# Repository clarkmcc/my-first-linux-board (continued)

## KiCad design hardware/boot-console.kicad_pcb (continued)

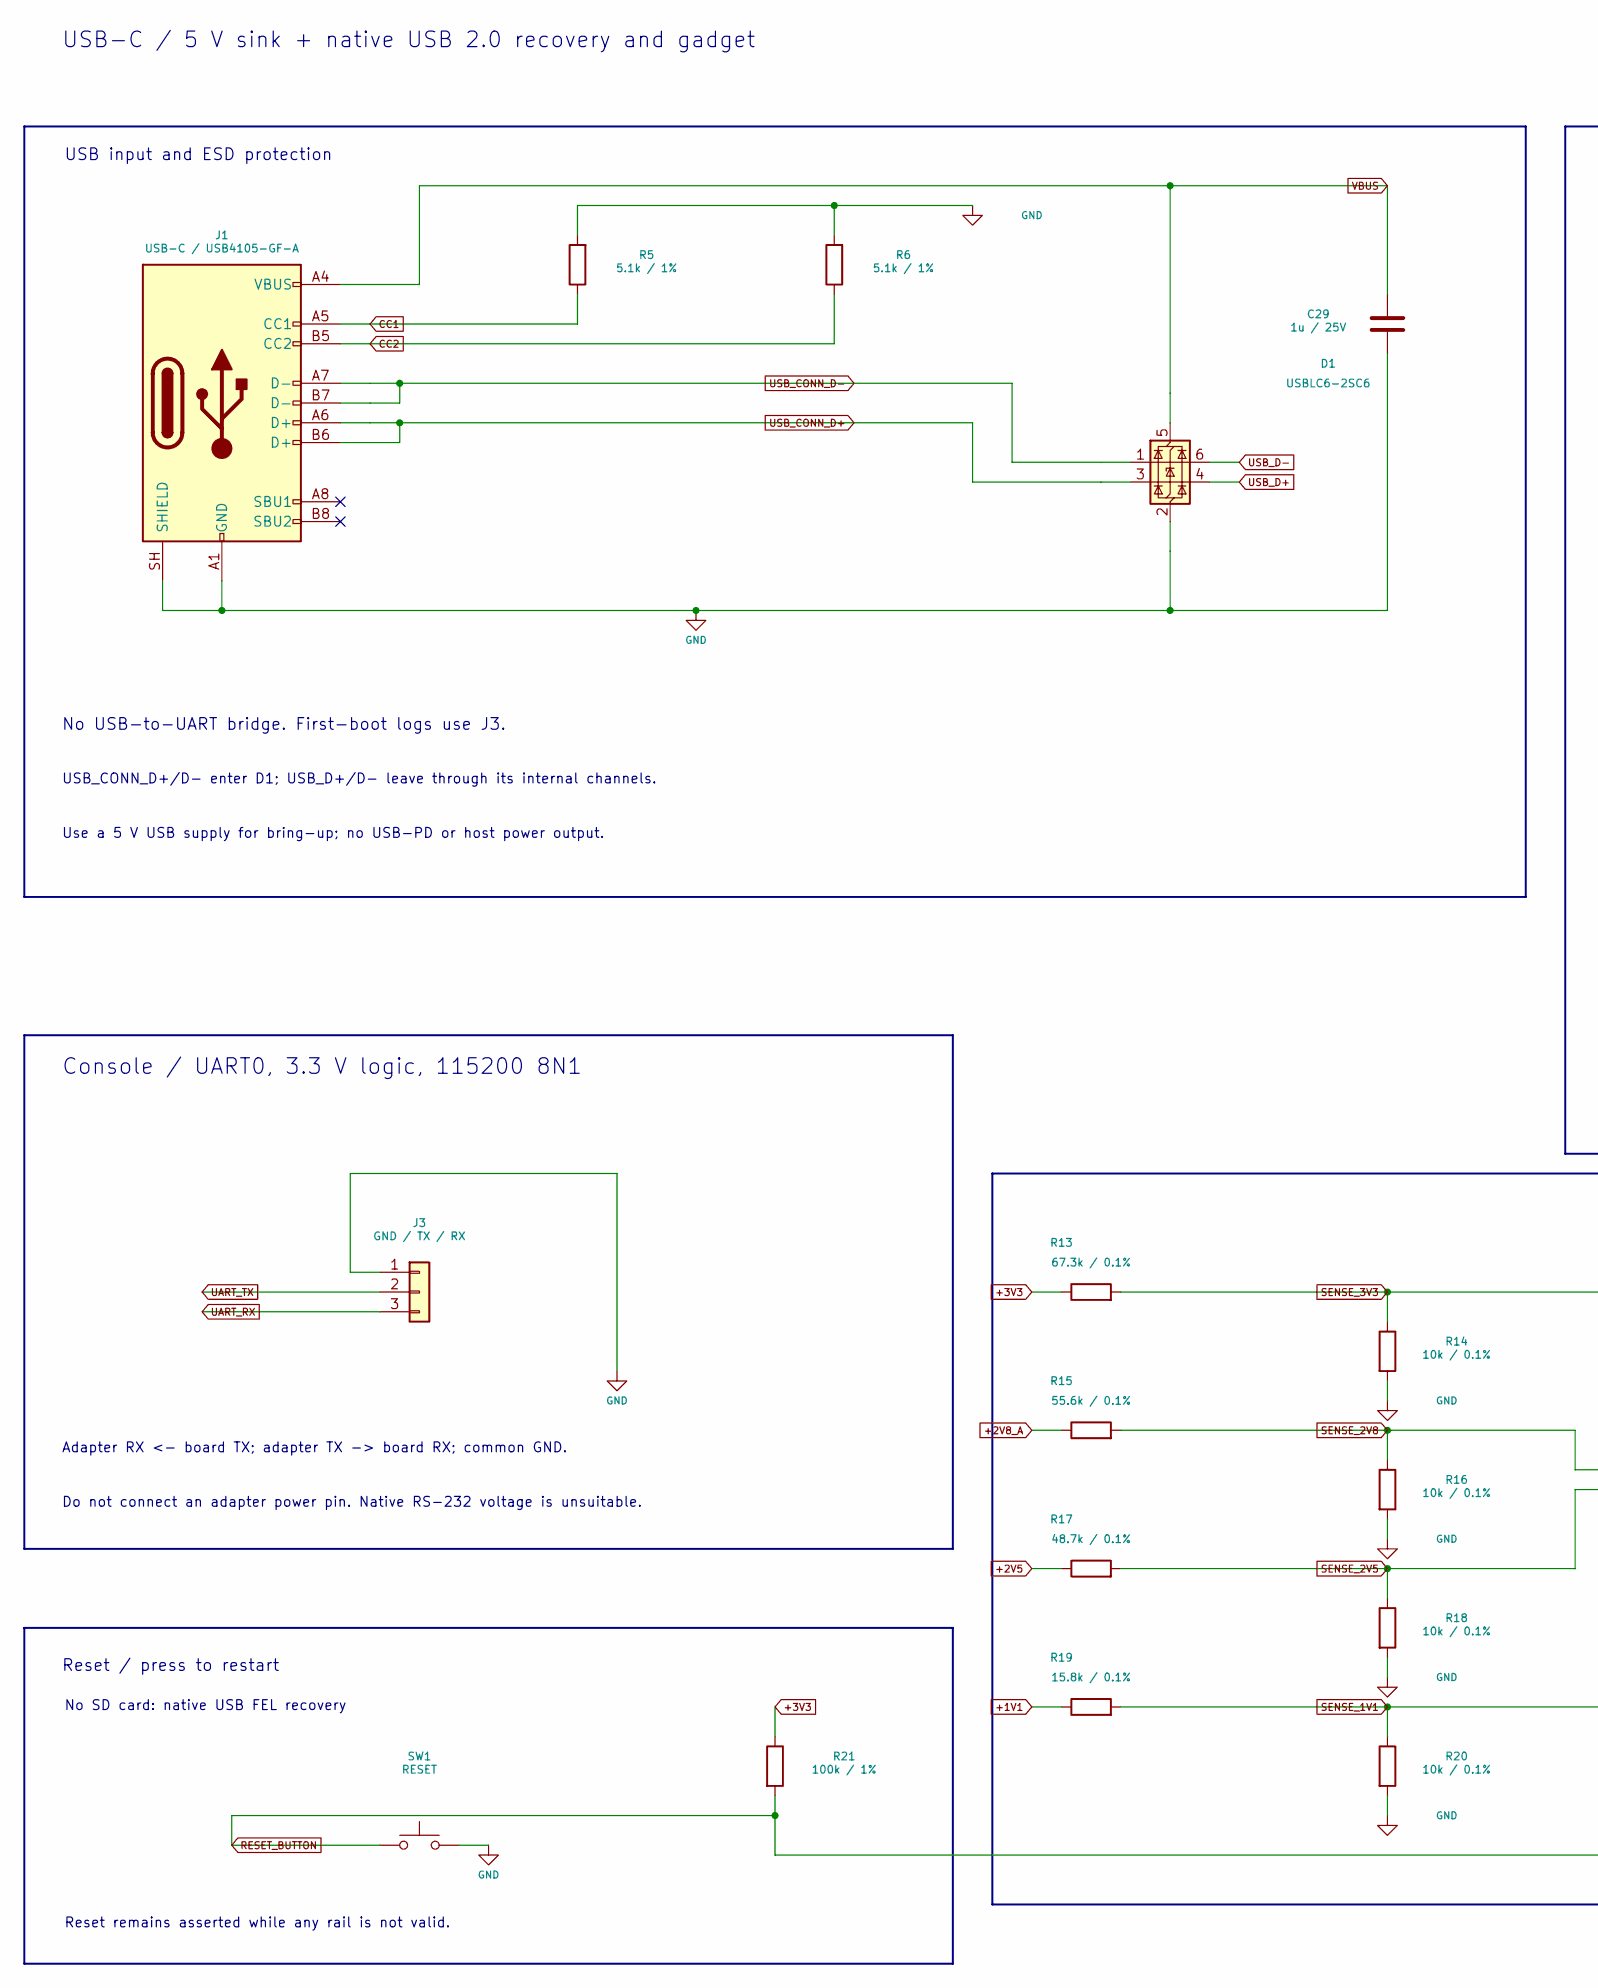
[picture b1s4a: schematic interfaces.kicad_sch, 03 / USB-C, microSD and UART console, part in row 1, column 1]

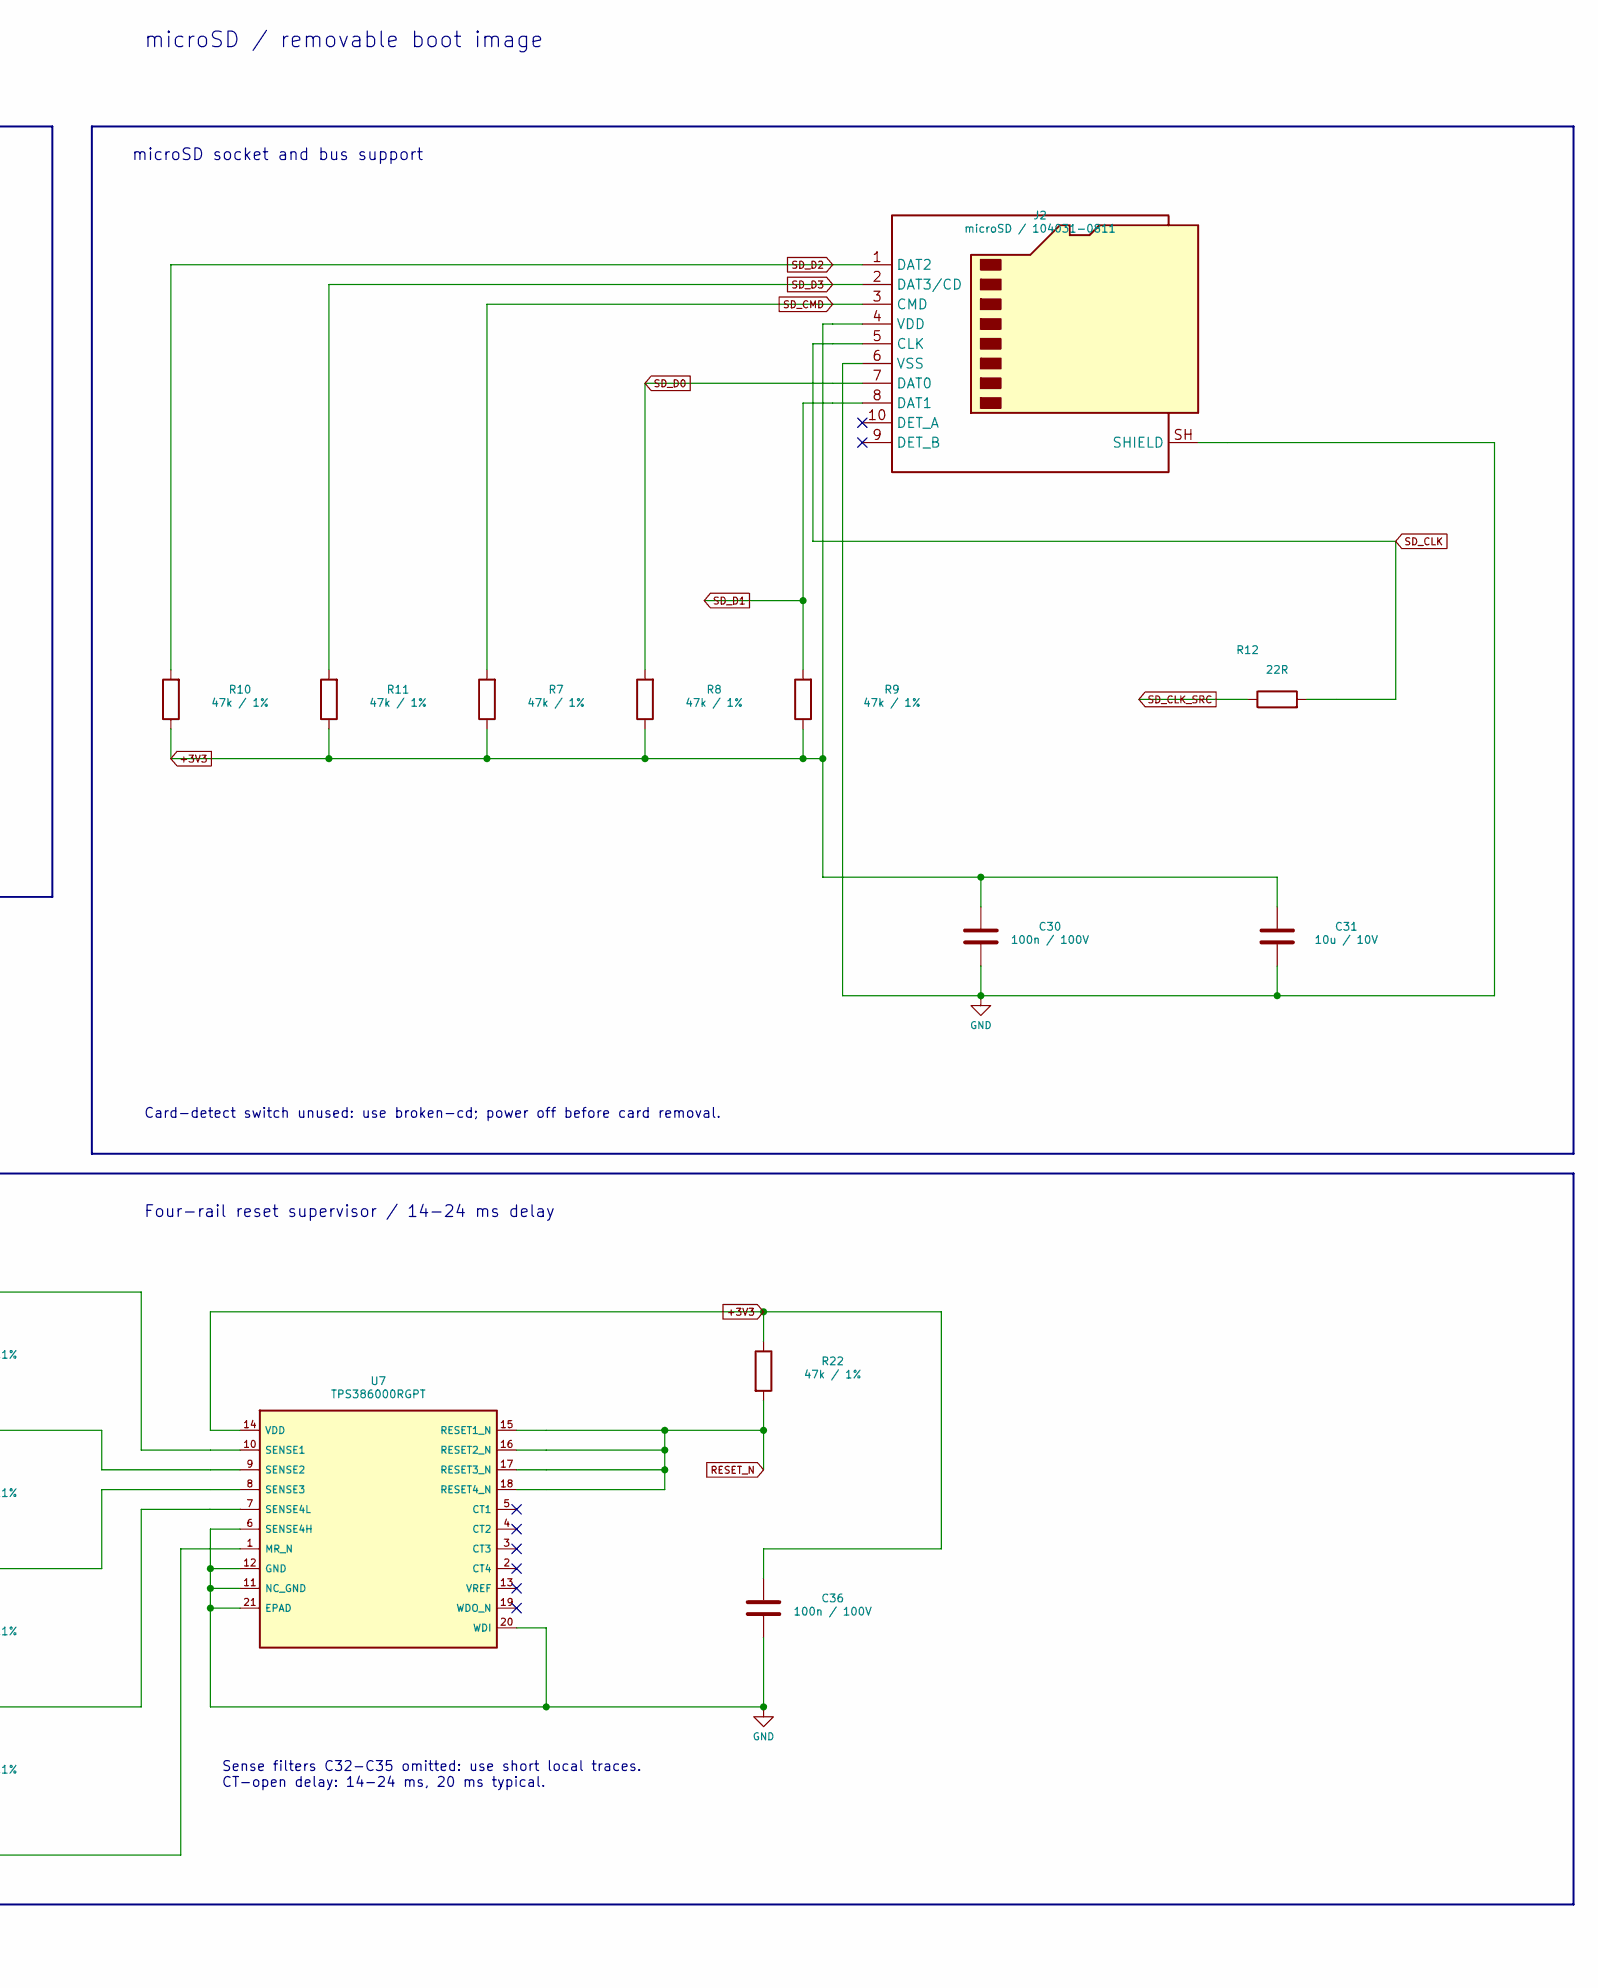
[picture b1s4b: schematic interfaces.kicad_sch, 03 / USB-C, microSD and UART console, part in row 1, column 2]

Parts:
C29: 1u / 25V; C_0603_1608Metric; MPN C1608X7R1E105K080AB
C30, C36: 100n / 100V; C_0603_1608Metric; MPN GRM188R72A104KA35D
C31: 10u / 10V; C_0805_2012Metric; MPN C2012X5R1A106M085AB
D1: USBLC6-2SC6; SOT-23-6; MPN USBLC6-2SC6
J1: USB-C / USB4105-GF-A; USB_C_Receptacle_GCT_USB4105-xx-A_16P_TopMnt_Horizontal; MPN USB4105-GF-A
J2: microSD / 104031-0811; microSD_HC_Molex_104031-0811; MPN 104031-0811
J3: GND / TX / RX; PinHeader_1x03_P2.54mm_Vertical; MPN TSW-103-07-G-S
R5, R6: 5.1k / 1%; R_0603_1608Metric; MPN CR0603-FX-5101ELF
R7, R8, R9, R10, R11, R22: 47k / 1%; R_0603_1608Metric; MPN RC0603FR-0747KL
R12: 22R; R_0603_1608Metric; MPN CRCW060322R0FKEA
R13: 67.3k / 0.1%; R_0603_1608Metric; MPN RN73R1JTTD6732B25
R14, R16, R20: 10k / 0.1%; R_0603_1608Metric; MPN RT0603BRD0710KL
R15: 55.6k / 0.1%; R_0603_1608Metric; MPN TNPW060355K6BEEA
R17: 48.7k / 0.1%; R_0603_1608Metric; MPN RQ73C1J48K7BTDF
R18: 10k / 0.1%; R_0603_1608Metric; MPN TNPW060310K0BYEN
R19: 15.8k / 0.1%; R_0603_1608Metric; MPN RG1608P-1582-B-T5
R21: 100k / 1%; R_0603_1608Metric; MPN RC0603FR-07100KL
SW1: RESET; SW_SPST_TL3305A; MPN TL3305AF160QG
U7: TPS386000RGPT; TPS386000_RGP20_EP2.8; MPN TPS386000RGPT

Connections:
+1V1: R19.1; also elsewhere on the board
+2V5: R17.1; also elsewhere on the board
+2V8_A: R15.1; also elsewhere on the board
+3V3: C30.1, C31.1, C36.1, J2.4 (VDD), R7.1, R8.1, R9.1, R10.1, R11.1, R13.1, R21.1, R22.1, U7.14 (VDD); also elsewhere on the board
CC1: J1.A5 (CC1), R5.1
CC2: J1.B5 (CC2), R6.1
GND: C29.2, C30.2, C31.2, C36.2, D1.2 (GND), J1.A1 (GND), J1.A12 (GND), J1.B1 (GND), J1.B12 (GND), J1.SH (SHIELD), J2.6 (VSS), J2.SH (SHIELD), J3.1, R5.2, R6.2, R14.2, R16.2, R18.2, R20.2, SW1.2, U7.6 (SENSE4H), U7.11 (NC_GND), U7.12 (GND), U7.20 (WDI), U7.21 (EPAD); also elsewhere on the board
RESET_BUTTON: R21.2, SW1.1, U7.1 (MR_N)
RESET_N: R22.2, U7.15 (RESET1_N), U7.16 (RESET2_N), U7.17 (RESET3_N), U7.18 (RESET4_N); also elsewhere on the board
SD_CLK: J2.5 (CLK), R12.2
SD_CLK_SRC: R12.1; also elsewhere on the board
SD_CMD: J2.3 (CMD), R7.2; also elsewhere on the board
SD_D0: J2.7 (DAT0), R8.2; also elsewhere on the board
SD_D1: J2.8 (DAT1), R9.2; also elsewhere on the board
SD_D2: J2.1 (DAT2), R10.2; also elsewhere on the board
SD_D3: J2.2 (DAT3/CD), R11.2; also elsewhere on the board
SENSE_1V1: R19.2, R20.1, U7.7 (SENSE4L)
SENSE_2V5: R17.2, R18.1, U7.8 (SENSE3)
SENSE_2V8: R15.2, R16.1, U7.9 (SENSE2)
SENSE_3V3: R13.2, R14.1, U7.10 (SENSE1)
UART_RX: J3.3; also elsewhere on the board
UART_TX: J3.2; also elsewhere on the board
USB_CONN_D+: D1.3 (I/O2), J1.A6 (D+), J1.B6 (D+)
USB_CONN_D-: D1.1 (I/O1), J1.A7 (D-), J1.B7 (D-)
USB_D+: D1.4 (I/O2); also elsewhere on the board
USB_D-: D1.6 (I/O1); also elsewhere on the board
VBUS: C29.1, D1.5 (VBUS), J1.A4 (VBUS), J1.A9 (VBUS), J1.B4 (VBUS), J1.B9 (VBUS); also elsewhere on the board

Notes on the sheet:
USB input and ESD protection
microSD socket and bus support
USB-C / 5 V sink + native USB 2.0 recovery and gadget
No USB-to-UART bridge. First-boot logs use J3.
USB_CONN_D+/D- enter D1; USB_D+/D- leave through its internal channels.
Use a 5 V USB supply for bring-up; no USB-PD or host power output.
microSD / removable boot image
Card-detect switch unused: use broken-cd; power off before card removal.
Console / UART0, 3.3 V logic, 115200 8N1
Adapter RX <- board TX; adapter TX -> board RX; common GND.
Do not connect an adapter power pin. Native RS-232 voltage is unsuitable.
Reset / press to restart
No SD card: native USB FEL recovery
Reset remains asserted while any rail is not valid.
Four-rail reset supervisor / 14-24 ms delay
Sense filters C32-C35 omitted: use short local traces. CT-open delay: 14-24 ms, 20 ms typical.

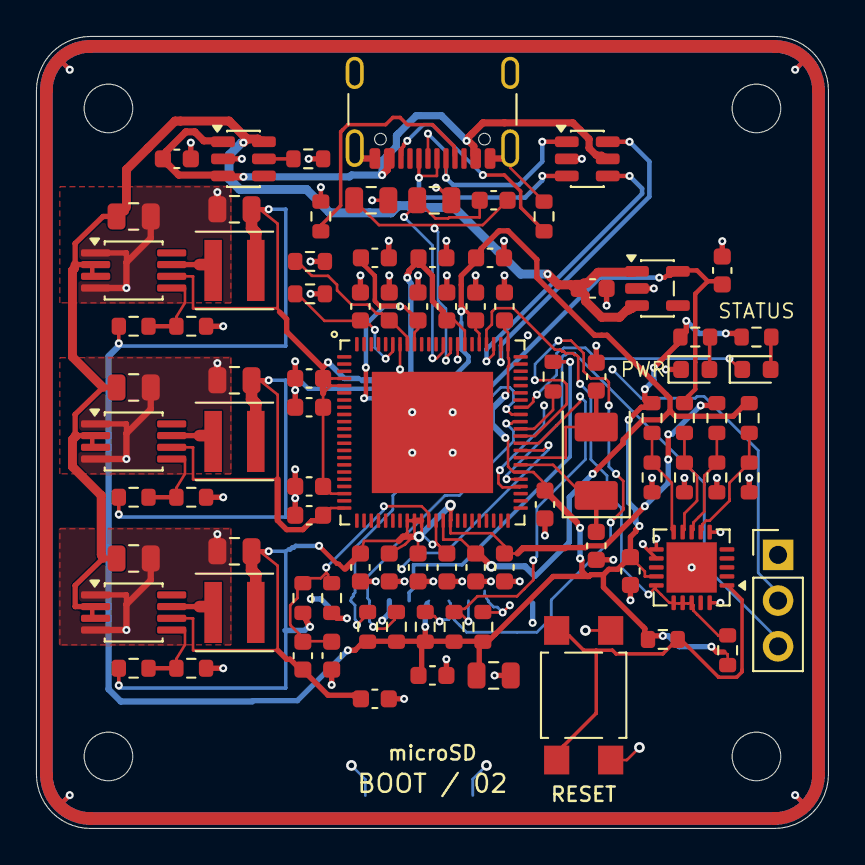
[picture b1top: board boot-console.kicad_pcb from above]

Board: 4 copper layers, 44.0 x 44.0 mm, 93 parts (1 on the bottom side), 45 nets.

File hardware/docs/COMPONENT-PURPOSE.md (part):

# Why each component exists

Every physical reference in the final board is listed below. Each explanation starts from the electrical or mechanical job the part performs; repeated bypass capacitors remain separate because their physical location serves a different current loop.

The board has 89 fitted electronic components and four M2.5 mounting holes. C32-C35 are intentionally absent.

| Reference | Value | Decision basis | Why it exists, from first principles | Evidence |
| --- | --- | --- | --- | --- |
| C1 | 30p / C0G / 1% | Functional | This capacitor supplies the oscillator input side of the crystal load network. Together with C2 and stray capacitance, it sets the load that determines crystal frequency. | XTAL |
| C2 | 30p / C0G / 1% | Functional | This capacitor supplies the oscillator output side of the crystal load network. Its initial 30 pF value needs confirmation with the assembled board, as does C1. | XTAL |
| C3 | 100n / 100V | Reliability | Fast interference can move the DDR comparison voltage and cause bit errors. C3 stores charge at that reference, reducing rapid voltage changes relative to ground. | REF |
| C4 | 100n / 100V | Reliability | The DDR reference must track half the memory supply, including fast supply changes. C4 and C3 form a capacitive divider that preserves this relationship. | REF |
| C5 | 100n / 100V | Reliability | Trace inductance prevents distant capacitors from supplying very fast current changes. C5 provides local charge for U1 pin 22, serving its processor core domain. | AW, REF |
| C6 | 100n / 100V | Reliability | Trace inductance prevents distant capacitors from supplying very fast current changes. C6 provides local charge for U1 pin 35, serving its processor core domain. | AW, REF |
| C7 | 100n / 100V | Reliability | Trace inductance prevents distant capacitors from supplying very fast current changes. C7 provides local charge for U1 pin 71, serving its processor core domain. | AW, REF |
| C8 | 4.7u / 10V | Reliability | The core supply can briefly demand more current than its regulator delivers through the connecting traces. This local 4.7 µF reservoir reduces voltage droop during those changes. | REF |
| C9 | 100n / 100V | Reliability | Trace inductance prevents distant capacitors from supplying very fast current changes. C9 provides local charge for U1 pin 30, serving its DDR memory domain. | AW, REF |
| C10 | 100n / 100V | Reliability | Trace inductance prevents distant capacitors from supplying very fast current changes. C10 provides local charge for U1 pin 31, serving its DDR memory domain. | AW, REF |
| C11 | 100n / 100V | Reliability | Trace inductance prevents distant capacitors from supplying very fast current changes. C11 provides local charge for U1 pin 32, serving its DDR memory domain. | AW, REF |
| C12 | 100n / 100V | Reliability | Trace inductance prevents distant capacitors from supplying very fast current changes. C12 provides local charge for U1 pin 34, serving its DDR memory domain. | AW, REF |
| C13 | 100n / 100V | Reliability | Trace inductance prevents distant capacitors from supplying very fast current changes. C13 provides local charge for U1 pin 36, serving its DDR memory domain. | AW, REF |
| C14 | 4.7u / 10V | Reliability | The DDR supply can briefly demand more current than its regulator delivers through the connecting traces. This local 4.7 µF reservoir reduces voltage droop during those changes. | REF |
| C15 | 100n / 100V | Reliability | Trace inductance prevents distant capacitors from supplying very fast current changes. C15 provides local charge for U1 pin 5, serving its I/O domain. | AW, REF |
| C16 | 100n / 100V | Reliability | Trace inductance prevents distant capacitors from supplying very fast current changes. C16 provides local charge for U1 pin 20, serving its I/O domain. | AW, REF |
| C17 | 100n / 100V | Reliability | Trace inductance prevents distant capacitors from supplying very fast current changes. C17 provides local charge for U1 pin 50, serving its I/O domain. | AW, REF |
| C18 | 100n / 100V | Reliability | Trace inductance prevents distant capacitors from supplying very fast current changes. C18 provides local charge for U1 pin 67, serving its USB domain. | AW, REF |
| C19 | 100n / 100V | Reliability | Trace inductance prevents distant capacitors from supplying very fast current changes. C19 provides local charge for U1 pin 4, serving its headphone supply domain. | AW, REF |
| C20 | 100n / 100V | Reliability | Trace inductance prevents distant capacitors from supplying very fast current changes. C20 provides local charge for U1 pin 73, serving its TV supply domain. | AW, REF |
| C21 | 4.7u / 10V | Reliability | The I/O supply can briefly demand more current than its regulator delivers through the connecting traces. This local 4.7 µF reservoir reduces voltage droop during those changes. | REF |
| C22 | 100n / 100V | Reliability | Trace inductance prevents distant capacitors from supplying very fast current changes. C22 provides local charge for U1 pin 80, serving its analog supply domain. | AW, REF |
| C23 | 4.7u / 10V | Reliability | The analog supply can briefly demand more current than its regulator delivers through the connecting traces. This local 4.7 µF reservoir reduces voltage droop during those changes. | REF |
| C24 | 1u / 25V | Reference precaution | This capacitor stores charge on the VRA1 analog reference, reducing rapid voltage changes. It preserves reference-board support for powered silicon, although its necessity with audio disabled is not documented. | REF |
| C25 | 1u / 25V | Reference precaution | This capacitor stores charge on the VRA2 analog reference, reducing rapid voltage changes. It preserves reference-board support for powered silicon, although its necessity with audio disabled is not documented. | REF |
| C26 | 10u / 10V | Reference precaution | This capacitor reduces rapid voltage changes on TV_VRN, an internal video reference brought outside U1. It preserves reference-board support, although its necessity with video disabled is not documented. | REF |
| C27 | 10u / 10V | Reference precaution | This capacitor reduces rapid voltage changes on TV_VRP, an internal video reference brought outside U1. It preserves reference-board support, although its necessity with video disabled is not documented. | REF |
| C28 | 1u / 25V | Reference precaution | This capacitor resists rapid changes in the voltage difference between the two video reference pins. It reproduces the reference circuit, but its necessity with video disabled is not documented. | REF |
| C29 | 1u / 25V | Reliability | Cable inductance resists sudden input-current changes, which can disturb the 5 V input. This capacitor supplies local charge at the power switch input without directly exposing the larger downstream capacitors. | SWITCH |
| C30 | 100n / 100V | Reliability | The microSD card draws fast current pulses that remote capacitors cannot supply through trace inductance. This 100 nF capacitor supplies those pulses beside the socket power pin. | SD, REF |
| C31 | 10u / 10V | Reliability | A microSD card also changes its current demand over longer intervals during internal operations. This 10 µF reservoir reduces local supply droop while the regulator responds. | SD, REF |
| C36 | 100n / 100V | Reliability | The reset supervisor also needs a steady supply to make dependable voltage decisions. This nearby capacitor supplies its fast current changes without relying on distant capacitors. | SUP |
| C37 | 10u / 10V | Architecture | The switching regulator draws input current in pulses. This nearby capacitor supplies those pulses, reducing input-voltage disturbance and the area of the high-current switching loop. | BUCK |
| C38 | 22u / 16V | Architecture | The inductor current does not exactly match the changing 1.1 V core load current. This output capacitor absorbs the difference and participates in the regulator control response. | BUCK |
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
